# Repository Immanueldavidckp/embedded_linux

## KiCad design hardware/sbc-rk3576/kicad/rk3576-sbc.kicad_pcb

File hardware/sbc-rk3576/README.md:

# RK3576 SBC: low-cost 8-core Linux board (LPDDR5, eMMC, NVMe, 4K HDMI, GbE, Wi-Fi)

A KiCad 9 single-board computer. The circuit lives in one Python file (`tools/design.py`), and the schematic,
PCB, BOM and placement files are generated from it, so they cannot drift apart.

| Requirement | Implementation |
|---|---|
| 8-core processor | **Rockchip RK3576**: 4× Cortex-A72 @ 2.2 GHz + 4× A53, Mali-G52 MC3, 6 TOPS NPU |
| LPDDR5, 4–8 GB | One LPDDR5 x32 315-ball package. 4 GB `MT62F1G32D2DS` or 8 GB `MT62F2G32D4DS`: **same footprint, BOM option** |
| eMMC | eMMC 5.1 HS400, 32 GB (64 GB option), boot device |
| NVMe M.2 | M.2 M-key 2230/2242, PCIe 2.1 ×1 |
| 4K display | HDMI 2.1 TX type-A: 4K@60 TMDS, 4K@120 FRL |
| UART | 3-pin debug UART0 header, **3.3 V**, 1 500 000 8N1 |
| USB | USB 3.0-A host + **2× USB 2.0-A** (FE1.1s hub) + USB-C (5 V in, OTG for maskrom/ADB) |
| Network (rev A1) | **Gigabit Ethernet** (RTL8211F + MagJack) and **Wi-Fi 5 + BT 4.2** (BL-M8821CU1, u.FL antenna) |
| Low price | **≈ $57 parts, ≈ $75 per built board** at 1k units (4 GB/32 GB, 10-layer PCB); ≈ $89 for 8 GB/64 GB. See [fab/cost_summary.md](fab/cost_summary.md) |

Also on the board: microSD (recovery boot), MASKROM/POWER/RESET keys, LEDs. It is **100 × 72 mm** with an
10-layer 1.6 mm stackup (rev A2; via-in-pad under the BGAs).

## Status

| Stage | State | Evidence |
|---|---|---|
| Architecture, parts, power tree | ✅ | [docs/design_notes.md](docs/design_notes.md) |
| Schematic: 14 sheets, 484 parts, 303 nets | ✅ ERC **0 errors / 0 warnings** | [docs/schematic.pdf](docs/schematic.pdf), [fab/erc.rpt](fab/erc.rpt) |
| RK3576 land pattern | ✅ real (LCSC C42388007): all 698 pad names = datasheet ball IDs | `kicad/sbc.pretty` |
| PMIC rail map | ✅ verified against mainline Linux `rk3576-rock-4d.dts` (same RK806S-5) | LOG.md #11 |
| Device tree | ✅ `software/rk3576-sbc.dts` compiles against mainline `rk3576.dtsi`; 7/7 GPIOs match the schematic | `tools/check_dts.sh` |
| Placement | ✅ all 484 footprints, 262 top / 222 bottom | renders in `docs/img/` |
| BGA fan-out | ✅ via-in-pad on every used ball: RK3576 + LPDDR5 (818) and eMMC (33) | `tools/fanout.py`, `tools/fanout_region.py` |
| Planes / pours | ✅ GND on L2/L6 + stitch vias; power pours on L5/L9 rebuilt as one connected region per rail | `tools/stitch.py`, `tools/pour_fix.py` |
| **Routing** | 🟡 **≈ 98.5 % done**: 10-layer rev A2, **14 of 942** connections still open (RGMII ×3, SD ×1, PCIe ×1, four PMIC control/feedback lines, a few power-pour joins) | [fab/drc.rpt](fab/drc.rpt), `tools/route_all.sh` |
| DRC | ✅ **0 errors** apart from the 14 unconnected items (warnings only: route tips at the open connections, locked fan-out vias, small pour islands) | [fab/drc.rpt](fab/drc.rpt) |
| Schematic ↔ PCB parity | ✅ 0 issues | [fab/drc.rpt](fab/drc.rpt) |
| Length / skew tuning | 🟡 **22 of 24** complete differential pairs within skew tolerance (HDMI, PCIe, USB 3/2, Ethernet, LPDDR5 CK/WCK/RDQS) by automatic meanders; LPDDR5 byte lanes still 8–11 mm apart (no free space for meanders) | [fab/tuning_report.md](fab/tuning_report.md), [fab/length_report.md](fab/length_report.md) |
| BOM, JLCPCB BOM, CPL | ✅ | `fab/` |
| Linux-PC readiness | ✅ on paper (Pi 4–5 class desktop) | [docs/linux_pc_readiness.md](docs/linux_pc_readiness.md) |

> **Do not order from `fab/gerbers-draft/` yet.** The board still needs the last 14 connections and
> length tuning of LPDDR5/HDMI/PCIe/USB3 (`tools/tune_length.py` does the pairs automatically; the
> LPDDR5 lanes need re-routing with length targets). See [docs/layout_guide.md](docs/layout_guide.md).

### How the board was routed (and what is left)

Freerouting stalled at 482 open connections. The board was then stripped back to fan-out + plane
stitching (942 open) and re-routed with tools written for this board (`tools/route_all.sh`):

1. `maze_route.py`: 25 µm grid, multi-layer A* in C, clearances from distance transforms; connections
   taken from KiCad's own DRC, so "done" means KiCad agrees. 942 → 168.
2. `fanout_region.py U701 --relocate`: the eMMC had never been fanned out; six bottom-side parts were
   slid off its via sites and every used ball got a via-in-pad.
3. `pour_fix.py`: power pours rebuilt as one connected region per rail: → 132.
4. `maze_ripup.py`: routes from the whole connected copper of each end (including dangling fan-out
   vias) with capped rip-up and reroute: → 78, DRC clean.
5. Slow nets (PMIC feedback/control, GPIO, UART, PHY interrupt) allowed onto the power layers
   (`--pwr-ok`), pours re-planned around them: → 72, DRC clean.
6. **Rev A2: 10 layers.** Four signal layers were full between the RK3576 and the LPDDR5, so two signal
   layers were added (`tools/stackup.py`, `tools/to_10layer.py` moved the routed board over intact):
   72 → 21 in one pass. Pieces that touch on the grid but not in KiCad are bridged, and nets stranded
   inside the BGA ball field are stripped and re-routed from their pads (`strip_routes.py --nets`): → 14.

7. `cleanup.py` removed routing debris, `tune_length.py` added 107 meanders (pairs into tolerance).

The last 14 are listed, with what blocks each one and how to finish it in KiCad's interactive router,
in [docs/layout_guide.md](docs/layout_guide.md#finishing-the-last-14-connections).

## Repository layout

```
hardware/sbc-rk3576/
├── tools/
│   ├── design.py           # THE CIRCUIT: every part, pin→net, MPN, price
│   ├── gen_lib.py          # symbols + footprints (custom + verified LCSC land patterns)
│   ├── gen_schematic.py    # 14-sheet hierarchical KiCad schematic
│   ├── gen_pcb.py          # stackup, outline, net classes, placement, planes
│   ├── fanout.py           # BGA via-in-pad escape
│   ├── stitch.py, pour.py  # GND stitching, power pours + stitching
│   ├── route_all.sh        # the routing pipeline (strip → maze → eMMC fan-out → pours → rip-up → clean → tune)
│   ├── maze_route.py, maze/astar.c, maze_ripup.py, maze_diag.py   # grid maze router + rip-up + diagnostics
│   ├── fanout_region.py, pour_fix.py, cleanup.py, tune_length.py  # eMMC fan-out, pours, debris, meanders
│   ├── route.py, import_ses.py   # earlier Freerouting flow (Specctra DSN/SES)
│   ├── length_report.py    # DDR/HS length + skew report
│   ├── gen_bom.py          # BOM, JLCPCB BOM, cost summary
│   ├── check_dts.sh        # compile the board device tree against mainline Linux
│   └── build.sh            # regenerate + ERC + DRC/parity + exports (REGEN_PCB=1 to re-place)
├── data/                   # ball maps (RK3576 698, LPDDR5 315, eMMC 153, RK806) + LCSC footprints
├── kicad/                  # KiCad 9 project (open rk3576-sbc.kicad_pro)
├── software/rk3576-sbc.dts # Linux device tree for this board
├── fab/                    # BOM, CPL, cost, ERC/DRC reports, length report, draft Gerbers
└── docs/                   # schematic PDF, assembly drawings, renders, design notes, guides
```

`tools/build.sh` regenerates the schematic and outputs **without** touching the routed PCB.
`REGEN_PCB=1 tools/build.sh` re-places the board from scratch, which throws away all routing.

## Sources

- RK3576 datasheet (pin list, package): [Rockchip RK3576 Datasheet V1.1](https://files.luckfox.com/wiki/Omni3576/PDF/Rockchip_RK3576_Datasheet_V1.1-20240430.pdf)
- Reference design: [Radxa ROCK 4D schematic V1.11](https://dl.radxa.com/rock4/4d/docs/hw/Radxa_ROCK_4D_SCH_V1.11.pdf) and mainline `arch/arm64/boot/dts/rockchip/rk3576-rock-4d.dts`
- eMMC 153b ballout: [Alliance Memory ASFC8G31M-51BIN](https://www.alliancememory.com/wp-content/uploads/AllianceMemory_8GB_ASFC8G31M-51BIN_eMMCdatasheet_November2022_v1.3.pdf)
- LPDDR5 315b package: [Micron 315b LPDDR5](https://www.mouser.com/datasheet/2/671/Micron_05092023_315b_y4bm_ddp_qdp_8dp_auto_lpddr5_-3175609.pdf)
- FE1.1s: [Terminus datasheet Rev 1.0](https://cdn-shop.adafruit.com/product-files/2991/FE1.1s+Data+Sheet+(Rev.+1.0).pdf)
- Land patterns: LCSC/EasyEDA C42388007 (RK3576), C187932 (RTL8211F), C9359 (FE1.1s), C50933 (HR911130C), C9900166844 (Wi-Fi module family)

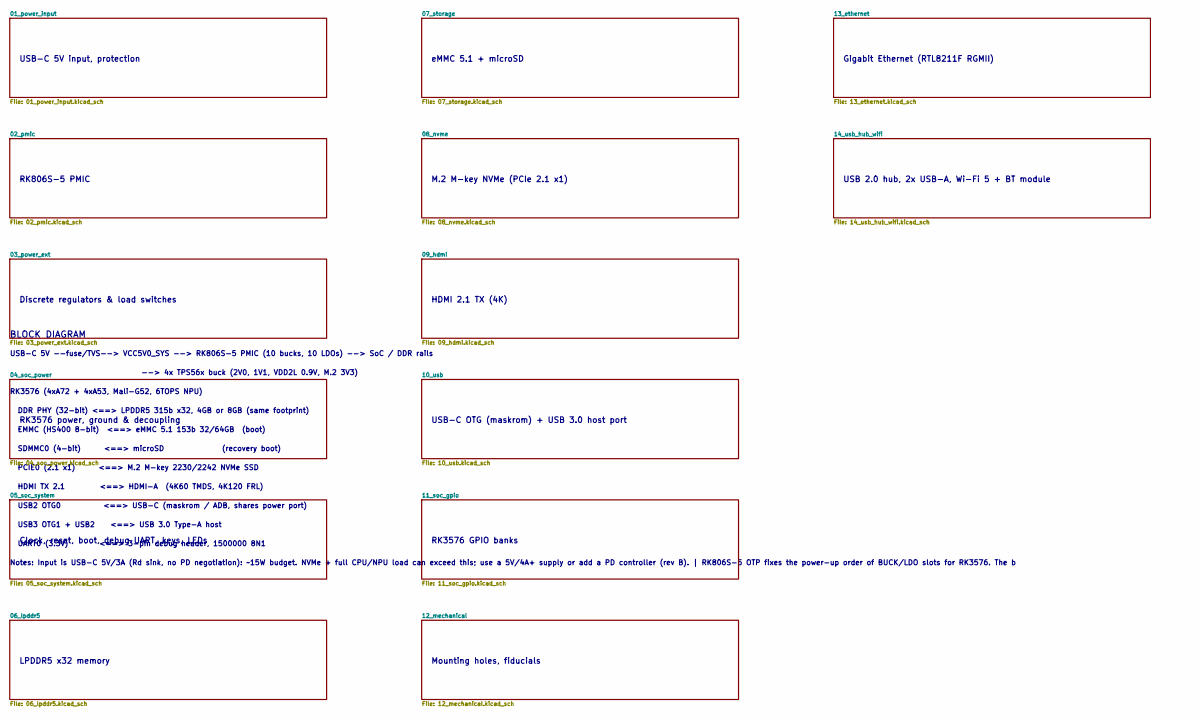
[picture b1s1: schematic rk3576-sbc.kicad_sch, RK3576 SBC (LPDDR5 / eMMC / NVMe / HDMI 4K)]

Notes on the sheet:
USB-C 5V input, protection
RK806S-5 PMIC
Discrete regulators & load switches
RK3576 power, ground & decoupling
Clock, reset, boot, debug UART, keys, LEDs
LPDDR5 x32 memory
eMMC 5.1 + microSD
M.2 M-key NVMe (PCIe 2.1 x1)
HDMI 2.1 TX (4K)
USB-C OTG (maskrom) + USB 3.0 host port
RK3576 GPIO banks
Mounting holes, fiducials
Gigabit Ethernet (RTL8211F RGMII)
USB 2.0 hub, 2x USB-A, Wi-Fi 5 + BT module
BLOCK DIAGRAM
USB-C 5V --fuse/TVS--> VCC5V0_SYS --> RK806S-5 PMIC (10 bucks, 10 LDOs) --> SoC / DDR rails
--> 4x TPS56x buck (2V0, 1V1, VDD2L 0.9V, M.2 3V3)
RK3576 (4xA72 + 4xA53, Mali-G52, 6TOPS NPU)
DDR PHY (32-bit) <==> LPDDR5 315b x32, 4GB or 8GB (same footprint)
EMMC (HS400 8-bit) <==> eMMC 5.1 153b 32/64GB (boot)
SDMMC0 (4-bit) <==> microSD (recovery boot)
PCIE0 (2.1 x1) <==> M.2 M-key 2230/2242 NVMe SSD
HDMI TX 2.1 <==> HDMI-A (4K60 TMDS, 4K120 FRL)
USB2 OTG0 <==> USB-C (maskrom / ADB, shares power port)
USB3 OTG1 + USB2 <==> USB 3.0 Type-A host
UART0 (3.3V) <==> 3-pin debug header, 1500000 8N1
Notes: Input is USB-C 5V/3A (Rd sink, no PD negotiation): ~15W budget. NVMe + full CPU/NPU load can exceed this; use a 5V/4A+ supply or add a PD controller (rev B). | RK806S-5 OTP fixes the power-up order of BUCK/LDO slots for RK3576. The b

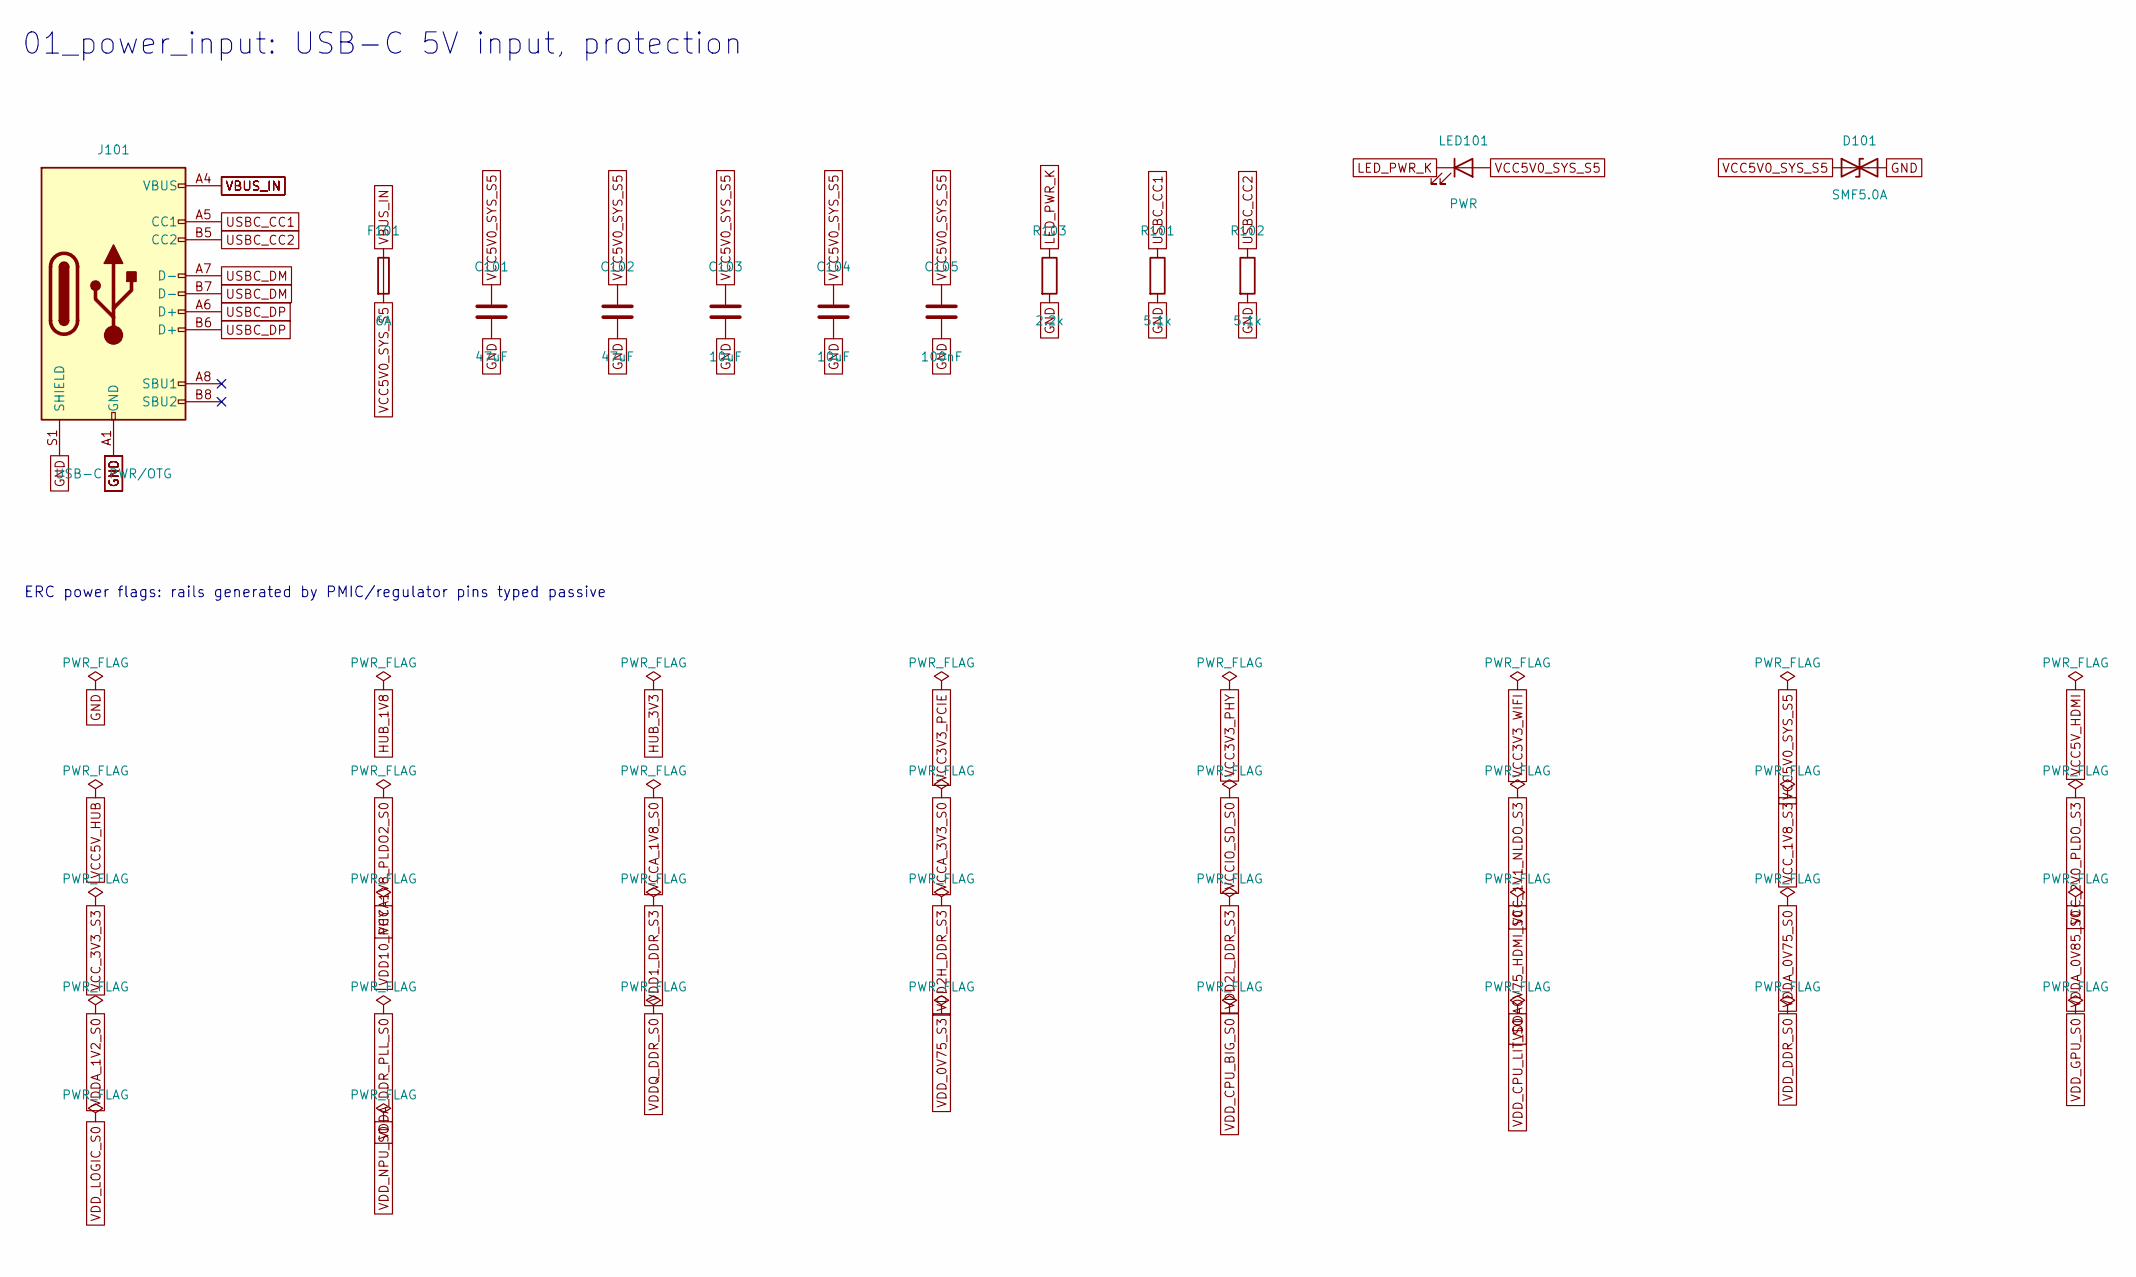
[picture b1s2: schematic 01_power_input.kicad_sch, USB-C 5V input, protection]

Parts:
C101, C102: 47uF; C_0805_2012Metric; MPN 0805 47uF 10V X5R
C103, C104: 10uF; C_0603_1608Metric; MPN 0603 10uF 10V X5R
C105: 100nF; C_0402_1005Metric; MPN 0402 100nF 10V X5R
D101: SMF5.0A; D_SOD-123F; MPN SMF5.0A; LCSC C123799
F101: 6A; Fuse_1206_3216Metric; MPN 1206L600/8SLY (6A fast)
J101: USB-C PWR/OTG; USB_C_Receptacle_HRO_TYPE-C-31-M-12; MPN TYPE-C-31-M-12; LCSC C165948
LED101: PWR; LED_0603_1608Metric; MPN 19-217/GHC-YR1S2/3T; LCSC C72043
R101, R102: 5.1k; R_0402_1005Metric; MPN 0402 5.1k 1%
R103: 2.2k; R_0402_1005Metric; MPN 0402 2.2k 1%

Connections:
GND: C101.2, C102.2, C103.2, C104.2, C105.2, D101.2 (A2), J101.A1 (GND), J101.A12 (GND), J101.B1 (GND), J101.B12 (GND), J101.S1 (SHIELD), R101.2, R102.2, R103.2; also elsewhere on the board
LED_PWR_K: LED101.1 (K), R103.1
USBC_CC1: J101.A5 (CC1), R101.1
USBC_CC2: J101.B5 (CC2), R102.1
USBC_DM: J101.A7 (D-), J101.B7 (D-); also elsewhere on the board
USBC_DP: J101.A6 (D+), J101.B6 (D+); also elsewhere on the board
VBUS_IN: F101.1, J101.A4 (VBUS), J101.A9 (VBUS), J101.B4 (VBUS), J101.B9 (VBUS); also elsewhere on the board
VCC5V0_SYS_S5: C101.1, C102.1, C103.1, C104.1, C105.1, D101.1 (A1), F101.2, LED101.2 (A); also elsewhere on the board

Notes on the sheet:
ERC power flags: rails generated by PMIC/regulator pins typed passive
01_power_input: USB-C 5V input, protection

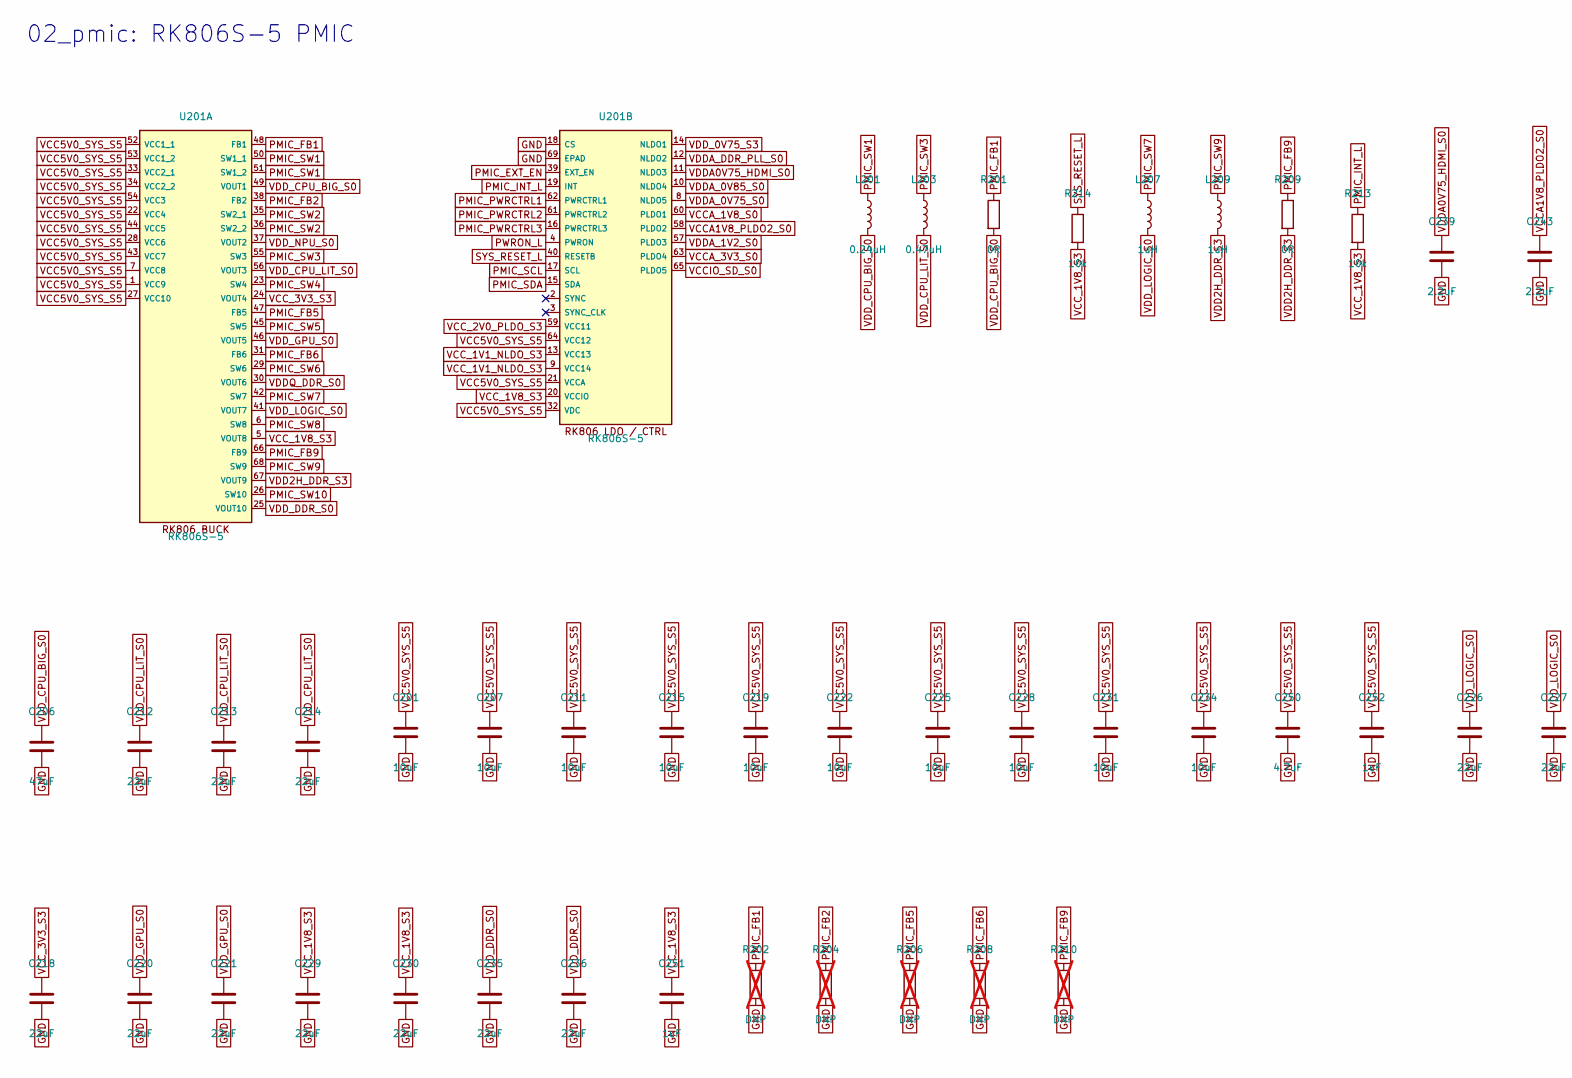
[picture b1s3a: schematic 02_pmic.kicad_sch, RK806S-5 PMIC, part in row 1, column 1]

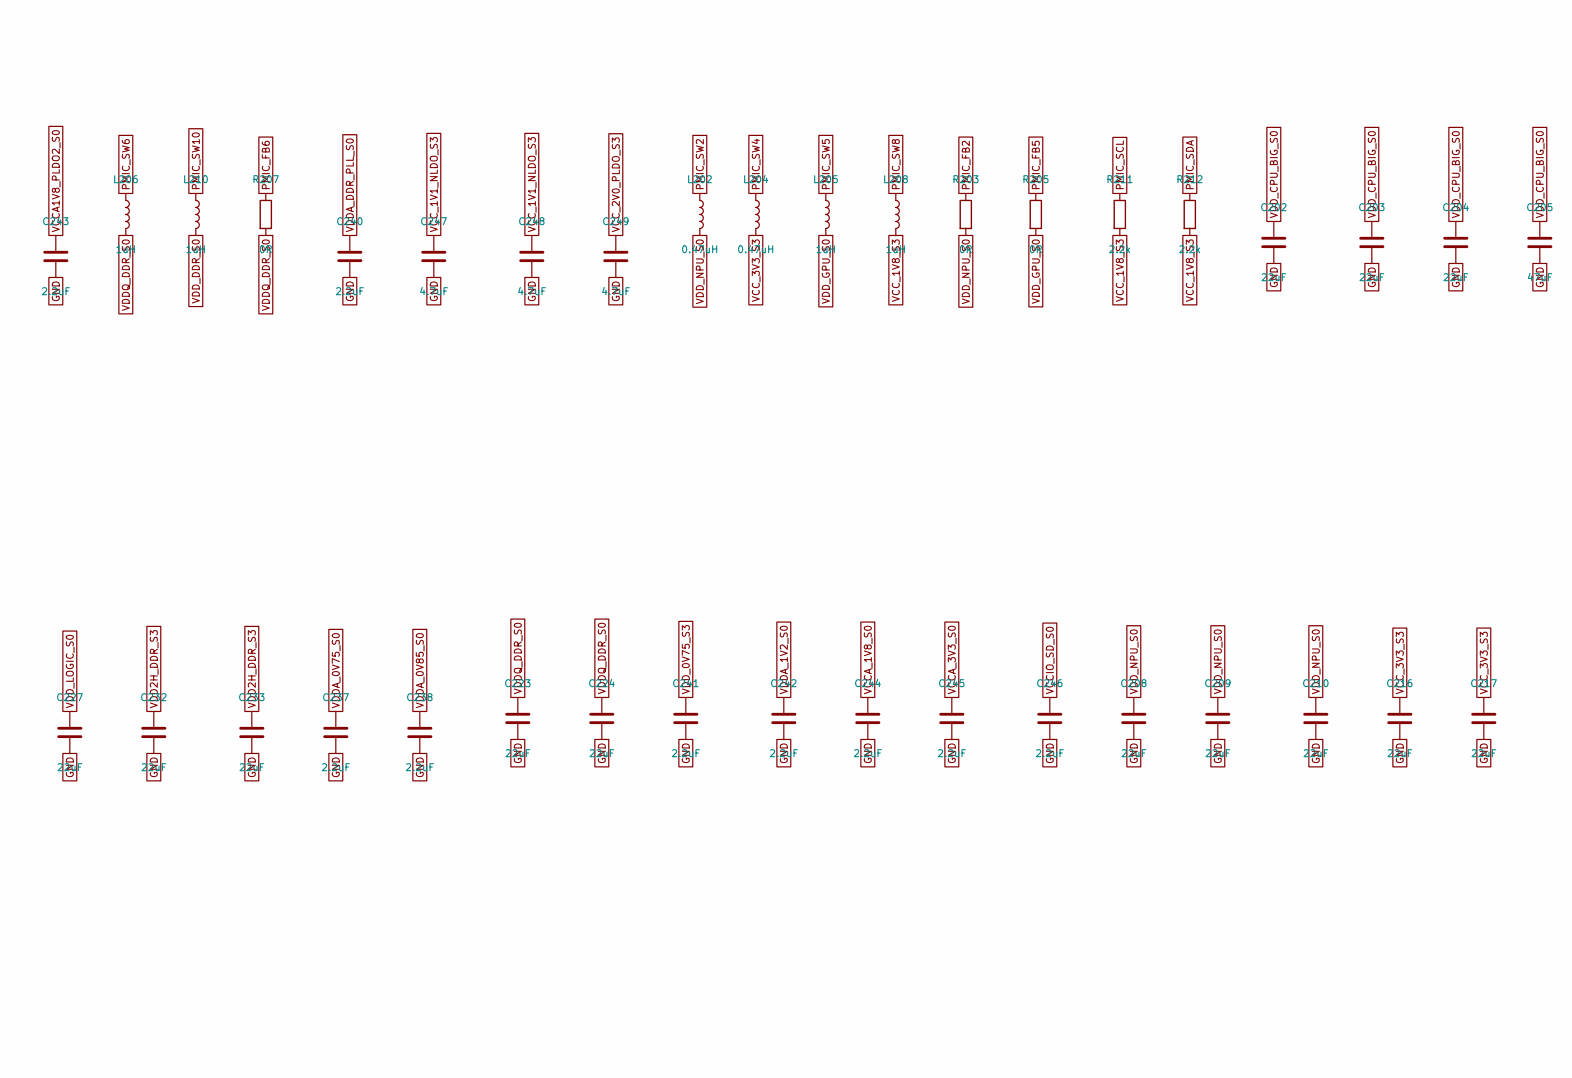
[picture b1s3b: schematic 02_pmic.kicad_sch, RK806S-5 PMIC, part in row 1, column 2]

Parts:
C201, C207, C211, C215, C219, C222, C225, C228, C231, C234: 10uF; C_0603_1608Metric; MPN 0603 10uF 10V X5R
C202, C203, C204, C208, C209, C210, C212, C213, C214, C216, C217, C218, C220, C221, C223, C224, C226, C227, C229, C230, C232, C233, C235, C236: 22uF; C_0603_1608Metric; MPN 0603 22uF 10V X5R
C205, C206: 47uF; C_0805_2012Metric; MPN 0805 47uF 10V X5R
C237, C238, C239, C240, C241, C242, C243, C244, C245, C246: 2.2uF; C_0402_1005Metric; MPN 0402 2.2uF 6.3V X5R
C247, C248, C249: 4.7uF; C_0402_1005Metric; MPN 0402 4.7uF 6.3V X5R
C250: 4.7uF; C_0402_1005Metric; MPN 0402 4.7uF 10V X5R
C251: 1uF; C_0402_1005Metric; MPN 0402 1uF 6.3V X5R
C252: 1uF; C_0402_1005Metric; MPN 0402 1uF 10V X5R
L201: 0.24uH; L_Coilcraft_XAL4030-XXX; MPN MDA4030-R24M (0.24uH 8A)
L202, L203, L204: 0.47uH; L_Coilcraft_XAL4030-XXX; MPN MDA4030-R47M (0.47uH 5.5A)
L205, L206, L207, L208, L209, L210: 1uH; L_Changjiang_FNR4030S; MPN FNR4030S1R0NT (1uH 3.4A)
R201, R203, R205, R207, R209: 0R; R_0402_1005Metric; MPN 0402 0R 1%
R202, R204, R206, R208, R210: DNP; R_0402_1005Metric; MPN 0402 DNP 1%; not fitted
R211, R212: 2.2k; R_0402_1005Metric; MPN 0402 2.2k 1%
R213, R214: 10k; R_0402_1005Metric; MPN 0402 10k 1%
U201: RK806S-5; QFN-68-1EP_8x8mm_P0.4mm_EP5.2x5.2mm_ThermalVias; MPN RK806S-5

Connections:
GND: C201.2, C202.2, C203.2, C204.2, C205.2, C206.2, C207.2, C208.2, C209.2, C210.2, C211.2, C212.2, C213.2, C214.2, C215.2, C216.2, C217.2, C218.2, C219.2, C220.2, C221.2, C222.2, C223.2, C224.2, C225.2, C226.2, C227.2, C228.2, C229.2, C230.2, C231.2, C232.2, C233.2, C234.2, C235.2, C236.2, C237.2, C238.2, C239.2, C240.2, C241.2, C242.2, C243.2, C244.2, C245.2, C246.2, C247.2, C248.2, C249.2, C250.2, C251.2, C252.2, R202.2, R204.2, R206.2, R208.2, R210.2, U201.18 (CS), U201.69 (EPAD); also elsewhere on the board
PMIC_EXT_EN: U201.39 (EXT_EN); also elsewhere on the board
PMIC_FB1: R201.1, R202.1, U201.48 (FB1)
PMIC_FB2: R203.1, R204.1, U201.38 (FB2)
PMIC_FB5: R205.1, R206.1, U201.47 (FB5)
PMIC_FB6: R207.1, R208.1, U201.31 (FB6)
PMIC_FB9: R209.1, R210.1, U201.66 (FB9)
PMIC_INT_L: R213.1, U201.19 (INT); also elsewhere on the board
PMIC_PWRCTRL1: U201.62 (PWRCTRL1); also elsewhere on the board
PMIC_PWRCTRL2: U201.61 (PWRCTRL2); also elsewhere on the board
PMIC_PWRCTRL3: U201.16 (PWRCTRL3); also elsewhere on the board
PMIC_SCL: R211.1, U201.17 (SCL); also elsewhere on the board
PMIC_SDA: R212.1, U201.15 (SDA); also elsewhere on the board
PMIC_SW1: L201.1, U201.50 (SW1_1), U201.51 (SW1_2)
PMIC_SW2: L202.1, U201.35 (SW2_1), U201.36 (SW2_2)
PMIC_SW3: L203.1, U201.55 (SW3)
PMIC_SW4: L204.1, U201.23 (SW4)
PMIC_SW5: L205.1, U201.45 (SW5)
PMIC_SW6: L206.1, U201.29 (SW6)
PMIC_SW7: L207.1, U201.42 (SW7)
PMIC_SW8: L208.1, U201.6 (SW8)
PMIC_SW9: L209.1, U201.68 (SW9)
PMIC_SW10: L210.1, U201.26 (SW10)
PWRON_L: U201.4 (PWRON); also elsewhere on the board
SYS_RESET_L: R214.1, U201.40 (RESETB); also elsewhere on the board
VCC5V0_SYS_S5: C201.1, C207.1, C211.1, C215.1, C219.1, C222.1, C225.1, C228.1, C231.1, C234.1, C250.1, C252.1, U201.1 (VCC9), U201.7 (VCC8), U201.21 (VCCA), U201.22 (VCC4), U201.27 (VCC10), U201.28 (VCC6), U201.32 (VDC), U201.33 (VCC2_1), U201.34 (VCC2_2), U201.43 (VCC7), U201.44 (VCC5), U201.52 (VCC1_1), U201.53 (VCC1_2), U201.54 (VCC3), U201.64 (VCC12); also elsewhere on the board
VCCA1V8_PLDO2_S0: C243.1, U201.58 (PLDO2); also elsewhere on the board
VCCA_1V8_S0: C244.1, U201.60 (PLDO1); also elsewhere on the board
VCCA_3V3_S0: C245.1, U201.63 (PLDO4); also elsewhere on the board
VCCIO_SD_S0: C246.1, U201.65 (PLDO5); also elsewhere on the board
VCC_1V1_NLDO_S3: C247.1, C248.1, U201.9 (VCC14), U201.13 (VCC13); also elsewhere on the board
VCC_1V8_S3: C229.1, C230.1, C251.1, L208.2, R211.2, R212.2, R213.2, R214.2, U201.5 (VOUT8), U201.20 (VCCIO); also elsewhere on the board
VCC_2V0_PLDO_S3: C249.1, U201.59 (VCC11); also elsewhere on the board
VCC_3V3_S3: C216.1, C217.1, C218.1, L204.2, U201.24 (VOUT4); also elsewhere on the board
VDD2H_DDR_S3: C232.1, C233.1, L209.2, R209.2, U201.67 (VOUT9); also elsewhere on the board
VDDA0V75_HDMI_S0: C239.1, U201.11 (NLDO3); also elsewhere on the board
VDDA_0V75_S0: C237.1, U201.8 (NLDO5); also elsewhere on the board
VDDA_0V85_S0: C238.1, U201.10 (NLDO4); also elsewhere on the board
VDDA_1V2_S0: C242.1, U201.57 (PLDO3); also elsewhere on the board
VDDA_DDR_PLL_S0: C240.1, U201.12 (NLDO2); also elsewhere on the board
VDDQ_DDR_S0: C223.1, C224.1, L206.2, R207.2, U201.30 (VOUT6); also elsewhere on the board
VDD_0V75_S3: C241.1, U201.14 (NLDO1); also elsewhere on the board
VDD_CPU_BIG_S0: C202.1, C203.1, C204.1, C205.1, C206.1, L201.2, R201.2, U201.49 (VOUT1); also elsewhere on the board
VDD_CPU_LIT_S0: C212.1, C213.1, C214.1, L203.2, U201.56 (VOUT3); also elsewhere on the board
VDD_DDR_S0: C235.1, C236.1, L210.2, U201.25 (VOUT10); also elsewhere on the board
VDD_GPU_S0: C220.1, C221.1, L205.2, R205.2, U201.46 (VOUT5); also elsewhere on the board
VDD_LOGIC_S0: C226.1, C227.1, L207.2, U201.41 (VOUT7); also elsewhere on the board
VDD_NPU_S0: C208.1, C209.1, C210.1, L202.2, R203.2, U201.37 (VOUT2); also elsewhere on the board

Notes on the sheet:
02_pmic: RK806S-5 PMIC

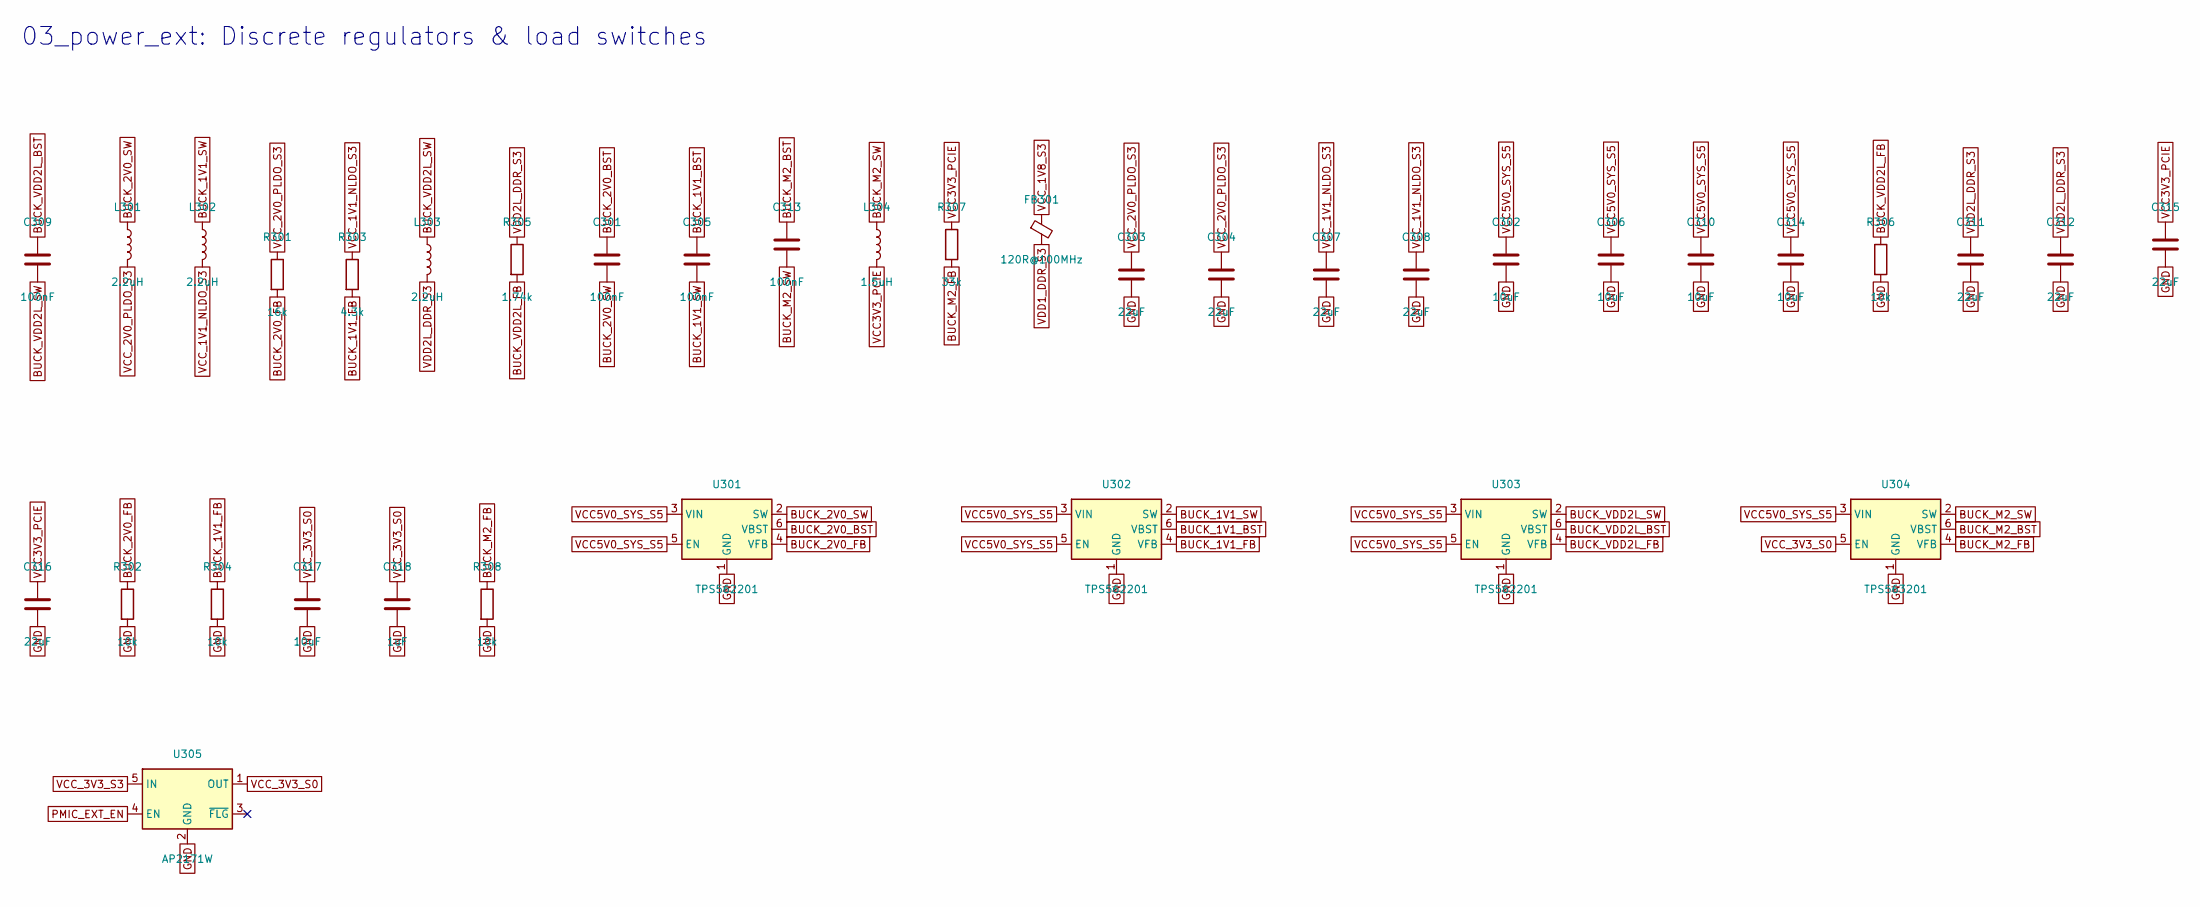
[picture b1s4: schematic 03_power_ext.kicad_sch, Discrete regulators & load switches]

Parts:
C301, C305, C309, C313: 100nF; C_0402_1005Metric; MPN 0402 100nF 6.3V X5R
C302, C306, C310, C314, C317: 10uF; C_0603_1608Metric; MPN 0603 10uF 10V X5R
C303, C304, C307, C308, C311, C312, C315, C316: 22uF; C_0603_1608Metric; MPN 0603 22uF 10V X5R
C318: 1uF; C_0402_1005Metric; MPN 0402 1uF 6.3V X5R
FB301: 120R@100MHz; L_0603_1608Metric; MPN BLM18PG121SN1D
L301, L302, L303: 2.2uH; L_Changjiang_FNR4030S; MPN FNR4030S2R2MT
L304: 1.5uH; L_Changjiang_FNR4030S; MPN FNR4030S1R5MT
R301: 16k; R_0402_1005Metric; MPN 0402 16k 1%
R302, R304, R306, R308: 10k; R_0402_1005Metric; MPN 0402 10k 1%
R303: 4.3k; R_0402_1005Metric; MPN 0402 4.3k 1%
R305: 1.74k; R_0402_1005Metric; MPN 0402 1.74k 1%
R307: 33k; R_0402_1005Metric; MPN 0402 33k 1%
U301, U302, U303: TPS562201; SOT-23-6; MPN TPS562201DDCR
U304: TPS563201; SOT-23-6; MPN TPS563201DDCR
U305: AP2171W; SOT-23-5; MPN AP2171WG-7; LCSC C155555

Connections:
BUCK_1V1_BST: C305.1, U302.6 (VBST)
BUCK_1V1_FB: R303.2, R304.1, U302.4 (VFB)
BUCK_1V1_SW: C305.2, L302.1, U302.2 (SW)
BUCK_2V0_BST: C301.1, U301.6 (VBST)
BUCK_2V0_FB: R301.2, R302.1, U301.4 (VFB)
BUCK_2V0_SW: C301.2, L301.1, U301.2 (SW)
BUCK_M2_BST: C313.1, U304.6 (VBST)
BUCK_M2_FB: R307.2, R308.1, U304.4 (VFB)
BUCK_M2_SW: C313.2, L304.1, U304.2 (SW)
BUCK_VDD2L_BST: C309.1, U303.6 (VBST)
BUCK_VDD2L_FB: R305.2, R306.1, U303.4 (VFB)
BUCK_VDD2L_SW: C309.2, L303.1, U303.2 (SW)
GND: C302.2, C303.2, C304.2, C306.2, C307.2, C308.2, C310.2, C311.2, C312.2, C314.2, C315.2, C316.2, C317.2, C318.2, R302.2, R304.2, R306.2, R308.2, U301.1 (GND), U302.1 (GND), U303.1 (GND), U304.1 (GND), U305.2 (GND); also elsewhere on the board
PMIC_EXT_EN: U305.4 (EN); also elsewhere on the board
VCC3V3_PCIE: C315.1, C316.1, L304.2, R307.1; also elsewhere on the board
VCC5V0_SYS_S5: C302.1, C306.1, C310.1, C314.1, U301.3 (VIN), U301.5 (EN), U302.3 (VIN), U302.5 (EN), U303.3 (VIN), U303.5 (EN), U304.3 (VIN); also elsewhere on the board
VCC_1V1_NLDO_S3: C307.1, C308.1, L302.2, R303.1; also elsewhere on the board
VCC_1V8_S3: FB301.1; also elsewhere on the board
VCC_2V0_PLDO_S3: C303.1, C304.1, L301.2, R301.1; also elsewhere on the board
VCC_3V3_S0: C317.1, C318.1, U304.5 (EN), U305.1 (OUT); also elsewhere on the board
VCC_3V3_S3: U305.5 (IN); also elsewhere on the board
VDD1_DDR_S3: FB301.2; also elsewhere on the board
VDD2L_DDR_S3: C311.1, C312.1, L303.2, R305.1; also elsewhere on the board

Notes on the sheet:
03_power_ext: Discrete regulators & load switches
